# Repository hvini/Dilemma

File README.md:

---

The Dilemma is a vertical stagger low-profile keyboard with mods.

## Table of contents

- [Features](#features)
- [Versions](#versions)
- [Required components](#required-components)
  - [3d prints - cases](#3d-prints---cases)
  - [Electronics](#electronics)
  - [Procyon mod](#procyon-mod)
  - [Cirque Trackpad mod](#cirque-trackpad-mod)
  - [Cases](#cases)
    - [Acrylic midplate (v2 only)](#acrylic-midplate-v2-only)
  - [Metal plates](#metal-plates)
  - [Community mods](#community-mods)
  - [Build guide](#build-guide)
  - [Forks](#forks)

---

# Features

- heavy pinky stagger
- MX and choc compatible
- version with hotswap
- underglow RGB, per-key RGB
- 2 Rotary encoders on thumb clusters
- connectors for OLED, LCD

# Versions

There are multiple versions of the dilemma:

| Folder          | Name                   | Size  | PCBA | Trackpad | Switches         | Additional features                          |
| --------------- | ---------------------- | ----- | ---- | -------- | ---------------- | -------------------------------------------- |
| `3x5_2`         | Dilemma DIY V2         | 3x5+2 | no   | Cirque   | MX, Choc V1      |                                              |
| `3x5_2_trackball` | Dilemma DIY V2 trackball | 3x5+2 | no | Cirque, trackball | MX, Choc V1 | [Trackball header](3x5_2_trackball/README.md) |
| `3x5_3`         | Dilemma V2             | 3x5+3 | yes  | Cirque   | MX, Choc V1      | Underglow, per-key RGB, rotary encoders      |
| `3x5_3_procyon` | Dilemma V3 hotswap     | 3x5+3 | yes  | Procyon  | Choc V1, hotswap | Underglow, per-key RGB, rotary encoders, VIK |
| `4x6_4`         | Dilemma MAX            | 4x6+4 | yes  | Cirque   | MX, Choc V1      | Underglow, per-key RGB, rotary encoders      |
| `4x6_4_procyon` | Dilemma MAX V3 hotswap | 4x6+4 | yes  | Procyon  | Choc V1, hotswap | Underglow, per-key RGB, rotary encodersk VIK |

# Required components

## 3d prints - cases

You can find the required 3d prints in the `mechanical` folder.

Most cases require a transparent mid layer to look good. You can either print it, or order it cut in acrylic.

## Electronics

The new revisions are made to be PCBA'd, you can find the gerber, BOM and POS files in the [Releases](https://github.com/bastardkb/dilemma/releases) section.

## Procyon mod

The `dilemma v3 hotswap` is made to work with a [Procyon PCB](https://github.com/bstiq/procyon).

## Cirque Trackpad mod

This mod uses I2C on the DIY version, and SPI on the assembled version.

The DIY version requires removing some resistors from the trackpad:

- R1
- R7 and R8 if you are using a microcontroller that runs on 5V

When installing the trackpad mod, you will need:

| Part name           | Amount | Link / source           |
| ------------------- | ------ | ----------------------- |
| M3 screw, torx, 6mm | 4      | Conrad                  |
| M3x5x5 screw insert | 4      | Aliexpress              |
| 3d printed parts    |        | See `mechanical` folder |
| 40mm cirque trackpad, curved    |        | |

If building the PCBA version, you will also need:

| Part name                                                     | Amount | Link / source |
| ------------------------------------------------------------- | ------ | ------------- |
| 12-position FPC cable, 0.5mm pitch, same side contacts, 100mm, type-B | 1      | Farnell       |

If building the DIY version, you will also need:

| Part name               | Amount | Link / source |
| ----------------------- | ------ | ------------- |
| SOD123 Resistor, 5kOhms | 2      |               |
| Cables                  |        |               |

## Cases

### Acrylic midplate (v2 only)

This case is only compatible with the assembled_v2 version !

Add an underglow effect and a beautiful view into the PCB with those acrylic midplates.

## Metal plates

Optional metal plates enables the use of tripods through magsafe magnets.

Order the [metal plates](mechanical/plates/v2/bottom_metal.dxf) in 3mm thickness. The metal needs to be *magnetized* !
Grab the appropriate DXF from the matched folder.

You will need:

| Part name              | Amount | Details           |
| ---------------------- | ------ | ----------------- |
| Metal plates           | 2      | 3mm               |
| Tripods                | 2      | Neewer Z flex     |
| Magsafe tripod adapter | 2      | Amazon/Aliexpress |

## Community mods

There are a range of community mods available (hex plates, covers...).

You can find more information in the readme in the `mechanical/community mods` folder.

## Build guide

https://docs.bastardkb.com/bg_dilemma/intro.html

## Forks

- [3x6 version](https://github.com/bstiq/Dilemma_3x6/)
- [3x5 + 3 version](https://github.com/dixls/Dilemma-3mod)

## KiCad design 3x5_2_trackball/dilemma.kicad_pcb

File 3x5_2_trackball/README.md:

# Dilemma DIY V2 - trackball

The `3x5_2` DIY board with its unused trackball connector (J7) placed and routed. Everything else, including the outline, is unchanged.

**Order:** upload `dilemma_3x5_2_trackball_gerber.zip`. The board is reversible, so one design makes both halves. On the left half, leave J7 empty.

KiCad files need KiCad 8 or newer.

Build guide with BOM, for OLED left and trackball right (Brazilian Portuguese): [guia_de_montagem.md](guia_de_montagem.md)

## J7 pinout

J7 is a 2x3, 2.54mm header with through-hole pads, so you can solder from either face. Each pin is labelled on the silkscreen.

| Pin | Silk | Signal   | Controller pin (RP2040) |
| --- | ---- | -------- | ----------------------- |
| 1   | V+   | Vcc      | VCC (3.3V)              |
| 2   | CK   | SPI SCK  | GP22                    |
| 3   | MI   | SPI MISO | GP20                    |
| 4   | MO   | SPI MOSI | GP23                    |
| 5   | CS   | SPI CS   | GP21                    |
| 6   | G    | GND      | GND                     |

These are the same GPIOs as the PCBA trackball schematic (`3x5_3_trackball/schematic.pdf`). The pin order differs from the J7 in the `3x5_2` schematic, because a 2x3 header needs this order to route without crossings.

Check that your sensor board accepts 3.3V on V+.

## Mechanical notes

- `mechanical/trackball` parts screw into H6-H9, the four Cirque mod holes. The hole pattern is the same as on the PCBA board.
- On the right half, the B.Cu face points up, so the holder goes on that face.
- The ball sits over the controller, so the holder can't be bolted flat. Raise it on M3x10 female-female standoffs. The 10mm is an estimate, so dry-fit the controller and sensor before final assembly.
- J7 sits under the holder plate. Solder wires directly, or use a low-profile header.
- Use `mechanical/cases/3x5_2/thin` as the case. The `3x5_3_trackball` case matches the switches, H2 and the USB opening, but its contour wall has no opening for the TRRS jack, and its bottom plate sits against the solder joints.
- J7 is close to the J3 battery connector: their courtyards overlap by 0.5mm, but the parts themselves should clear by about 0.45mm.

## Firmware

Trackball only: enable the PMW33xx driver on SPI0 with the pins above, and set the right half as the pointing side.

Cirque on the left and trackball on the right: QMK allows one `POINTING_DEVICE_DRIVER` per build, so this needs `POINTING_DEVICE_DRIVER = custom` with your own code calling both sensors. No firmware is included here, and this combination has not been tested.

## Trackball parts

Sizes are measured from the STLs; the repo has no parts list.

| Part                                   | Qty | Notes                                 |
| -------------------------------------- | --- | ------------------------------------- |
| PMW3360 board with LM19-LSI lens       | 1   | Must fit under the holder's 19x24mm window |
| 34mm trackball                         | 1   | Holder cavity fits a 34mm ball        |
| MR63ZZ bearing (3x6x2.5mm)             | 3   | Size inferred from the 2.6mm wide slots |
| 3mm pin, 8mm long                      | 3   | Bearing axles                         |
| M3 screws, nuts and standoffs          | 4   | Length depends on the standoff height |

The holder has no screw posts for the sensor board. The board has to be fixed under the plate with the lens in the window, about 2.4mm from the ball (datasheet figure, from memory).

To reuse a Charybdis sensor PCB with the unmodified `mechanical/trackball` parts:

- The board is about 42mm across, so it overlaps H7 and H8. Use only three standoffs, at H6, H7 and H9, and leave H8 empty.
- Place the lens in the holder window with the board's 6-pin header on the J7 side.
- Mark H7 on the board's rim through the holder's hole, then file a notch about 3mm deep there. This spot has no copper within about 6mm of the hole centre, but dry-fit before cutting.
- Fix the board under the plate with double-sided tape about 0.5mm thick. This also sets the lens height to match the Charybdis.
- Wire 3.3V to V+, GND to G, SCK to CK, MISO to MI, MOSI to MO and SS to CS.

## Assembly warnings

- Jumpers JP1-JP8: solder one face only, on the left half only. Each header pin has two jumpers, one per face, so soldering both shorts signals to power or GND.
- OLED on the left half: with the F-face jumpers (JP1, JP3, JP5, JP7) and the F face up, the O2 pins read SDA, SCL, VCC, GND from left to right, with the controller above O2. Check this against the labels on your module, because VCC and GND positions vary between modules.
- Fit the right half's reset button on the bottom face (F side). The top is covered by the holder.
- Never plug or unplug the TRRS cable with USB connected. It carries 3.3V.
- Under the PCB, use low-head M3 screws at H6, H7 and H9. The `3x5_2/thin` case has about 3.4mm of room there.

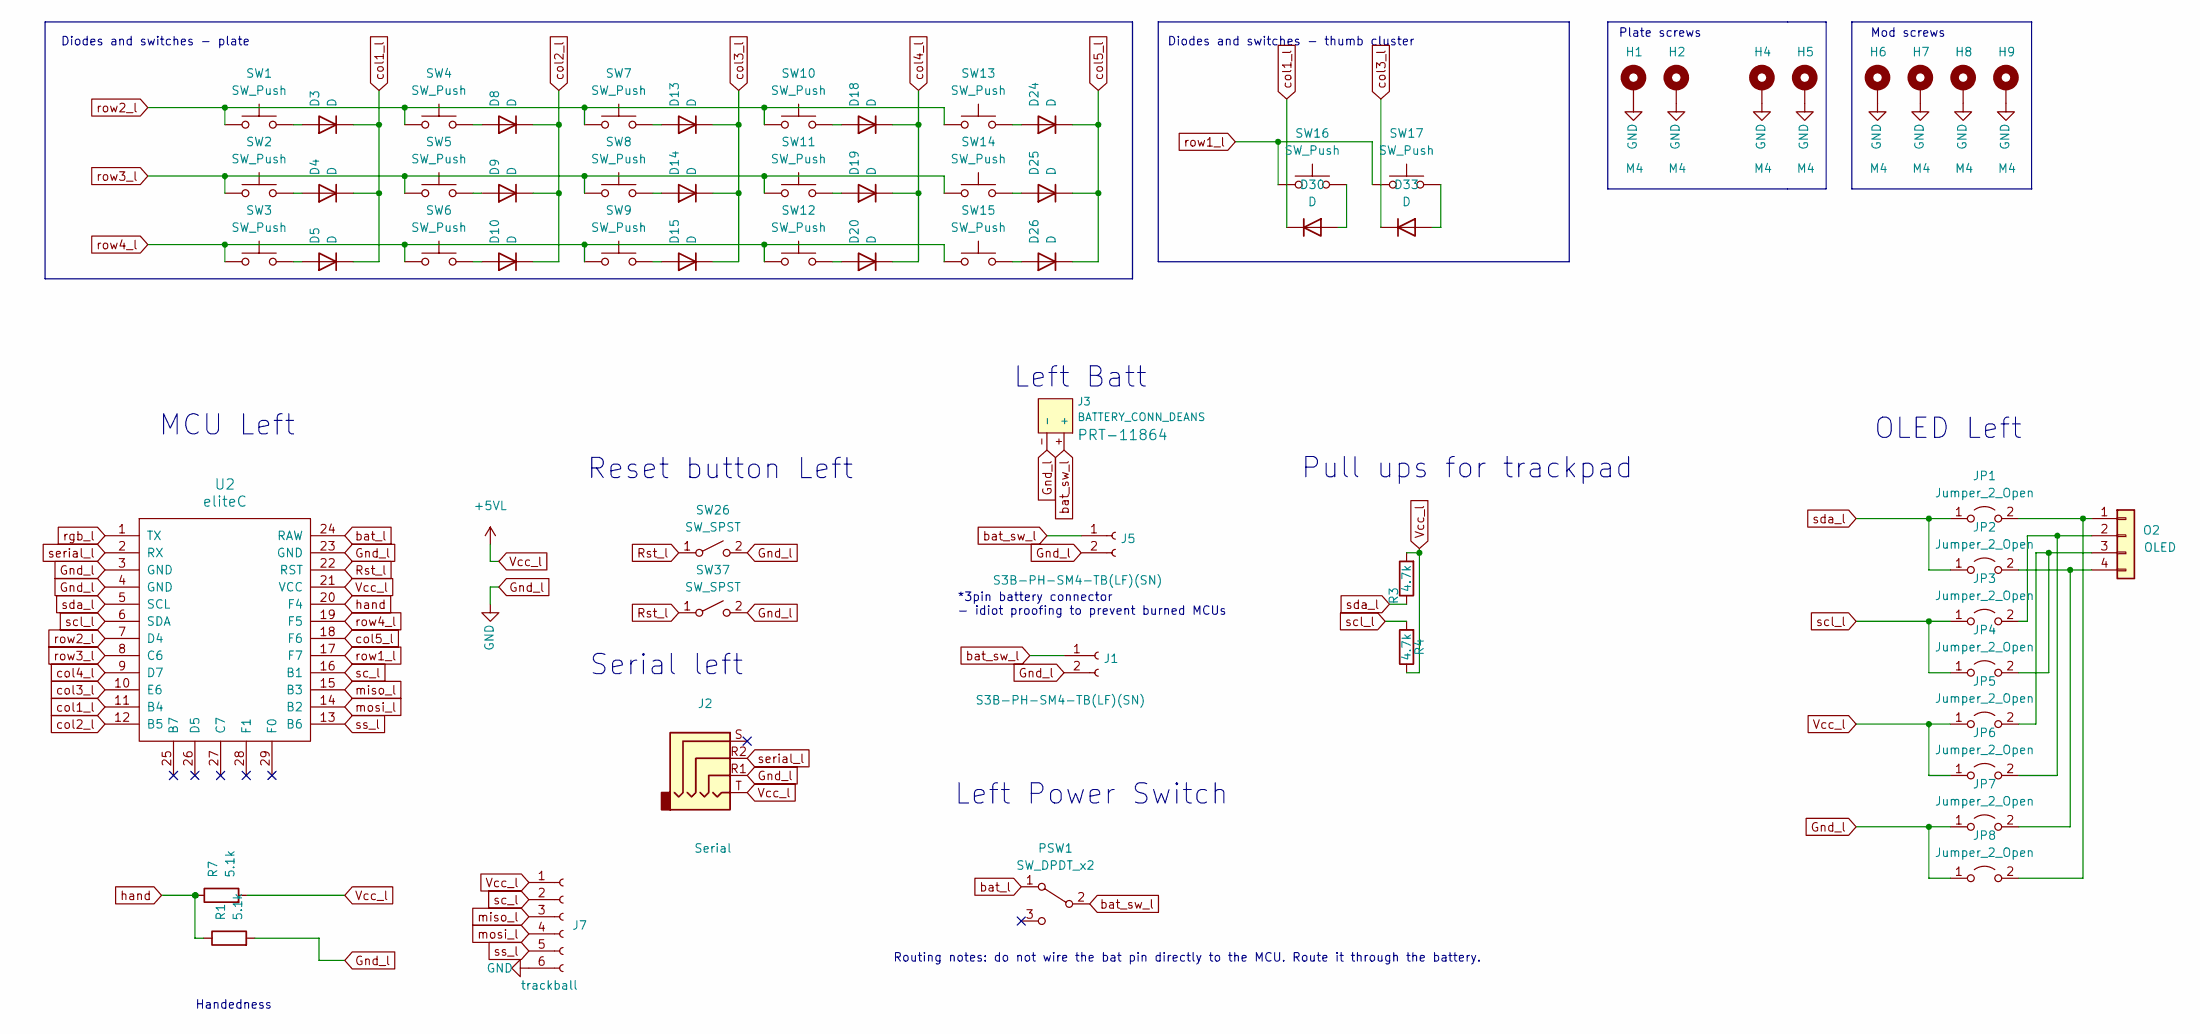
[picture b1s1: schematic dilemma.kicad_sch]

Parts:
D3, D4, D5, D8, D9, D10, D13, D14, D15, D18, D19, D20, D24, D25, D26, D30, D33: D; D_1206_handsolder_reversible
H1, H2, H4, H5, H6, H7, H8, H9: M4; MountingHole_3mm_Pad_thin
J1, J5: S3B-PH-SM4-TB(LF)(SN); JST_SH_BM02B-SRSS-TB_1x02-1MP_P1.00mm_Vertical; LCSC C265101
J2: Serial; Jack_3.5mm_PJ320E_Horizontal_reversible
J3: BATTERY_CONN_DEANS; battery_connector_THT
J7: trackball; PinHeader_2x03_P2.54mm_Vertical
JP1, JP2, JP3, JP4, JP5, JP6, JP7, JP8: Jumper_2_Open; SolderJumper-2_P1.3mm_Open_RoundedPad1.0x1.5mm
O2: OLED; PinHeader_1x04_P2.54mm_Vertical
PSW1: SW_DPDT_x2; Switch_MSK-12C01-07; LCSC C431540
R1, R7: 5.1k; R_1206_handsolder; JLCPCB BOM 1
R3, R4: 4.7k; R_1206_handsolder_reversible; LCSC C269746
SW1, SW2, SW3, SW4, SW5, SW6, SW7, SW8, SW9, SW10, SW11, SW12, SW13, SW14, SW15, SW16, SW17: SW_Push; SW_MX_choc
SW26, SW37: SW_SPST; SW_Push_1P1T_NO_6x6mm_H9.5mm
U2: eliteC; pro-micro

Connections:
Gnd_l: H1.1, H2.1, H4.1, H5.1, H6.1, H7.1, H8.1, H9.1, J1.2, J2.R1, J3.-, J5.2, J7.6, JP7.1 (A), JP8.1 (A), R1.2, SW26.2 (B), SW37.2 (B), U2.3 (GND), U2.4 (GND), U2.23 (GND)
unnamed: D3.2 (A), SW1.2
unnamed: D4.2 (A), SW2.2
unnamed: D5.2 (A), SW3.2
unnamed: D8.2 (A), SW4.2
unnamed: D9.2 (A), SW5.2
unnamed: D10.2 (A), SW6.2
unnamed: D13.2 (A), SW7.2
unnamed: D14.2 (A), SW8.2
unnamed: D15.2 (A), SW9.2
unnamed: D18.2 (A), SW10.2
unnamed: D19.2 (A), SW11.2
unnamed: D20.2 (A), SW12.2
unnamed: D24.2 (A), SW13.2
unnamed: D25.2 (A), SW14.2
unnamed: D26.2 (A), SW15.2
unnamed: D30.2 (A), SW16.2
unnamed: D33.2 (A), SW17.2
unnamed: JP1.2 (B), JP8.2 (B), O2.1
unnamed: JP2.2 (B), JP7.2 (B), O2.4
unnamed: JP3.2 (B), JP6.2 (B), O2.2
unnamed: JP4.2 (B), JP5.2 (B), O2.3
Rst_l: SW26.1 (A), SW37.1 (A), U2.22 (RST)
Vcc_l: J2.T, J7.1, JP5.1 (A), JP6.1 (A), R3.2, R4.1, R7.2, U2.21 (VCC)
bat_l: PSW1.1 (A), U2.24 (RAW)
bat_sw_l: J1.1, J3.+, J5.1, PSW1.2 (B)
col1_l: D3.1 (K), D4.1 (K), D5.1 (K), D30.1 (K), U2.11 (B4)
col2_l: D8.1 (K), D9.1 (K), D10.1 (K), U2.12 (B5)
col3_l: D13.1 (K), D14.1 (K), D15.1 (K), D33.1 (K), U2.10 (E6)
col4_l: D18.1 (K), D19.1 (K), D20.1 (K), U2.9 (D7)
col5_l: D24.1 (K), D25.1 (K), D26.1 (K), U2.18 (F6)
hand: R1.1, R7.1, U2.20 (F4)
miso_l: J7.3, U2.15 (B3)
mosi_l: J7.4, U2.14 (B2)
rgb_l: U2.1 (TX)
row1_l: SW16.1, SW17.1, U2.17 (F7)
row2_l: SW1.1, SW4.1, SW7.1, SW10.1, SW13.1, U2.7 (D4)
row3_l: SW2.1, SW5.1, SW8.1, SW11.1, SW14.1, U2.8 (C6)
row4_l: SW3.1, SW6.1, SW9.1, SW12.1, SW15.1, U2.19 (F5)
sc_l: J7.2, U2.16 (B1)
scl_l: JP3.1 (A), JP4.1 (A), R4.2, U2.6 (SDA)
sda_l: JP1.1 (A), JP2.1 (A), R3.1, U2.5 (SCL)
serial_l: J2.R2, U2.2 (RX)
ss_l: J7.5, U2.13 (B6)

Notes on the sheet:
MCU Left
Left Batt
Handedness
Plate screws
Routing notes: do not wire the bat pin directly to the MCU. Route it through the battery.
Serial left
Diodes and switches - plate
Reset button Left
Pull ups for trackpad
Mod screws
Left Power Switch
OLED Left
Diodes and switches - thumb cluster
*3pin battery connector - idiot proofing to prevent burned MCUs

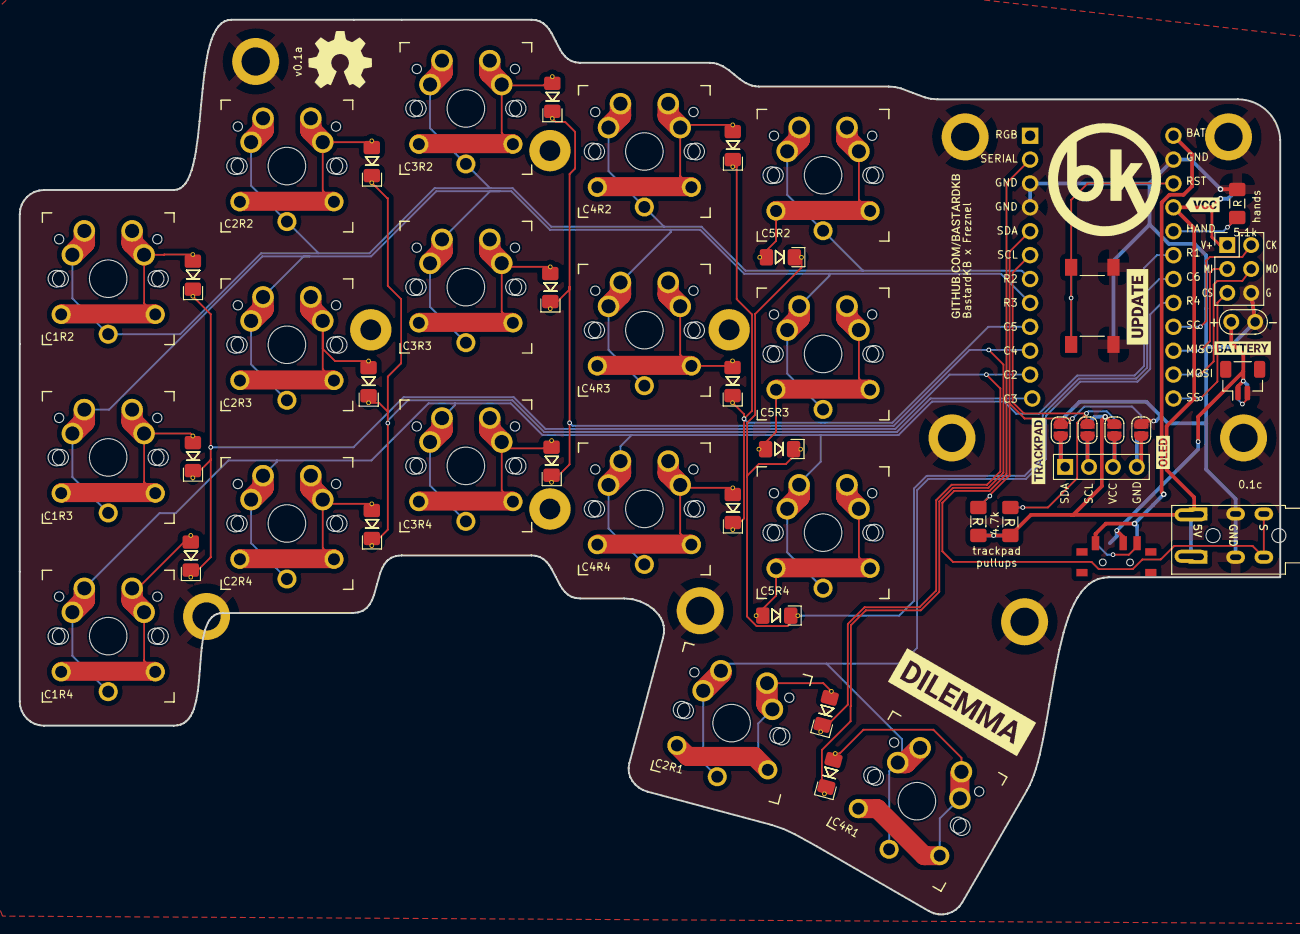
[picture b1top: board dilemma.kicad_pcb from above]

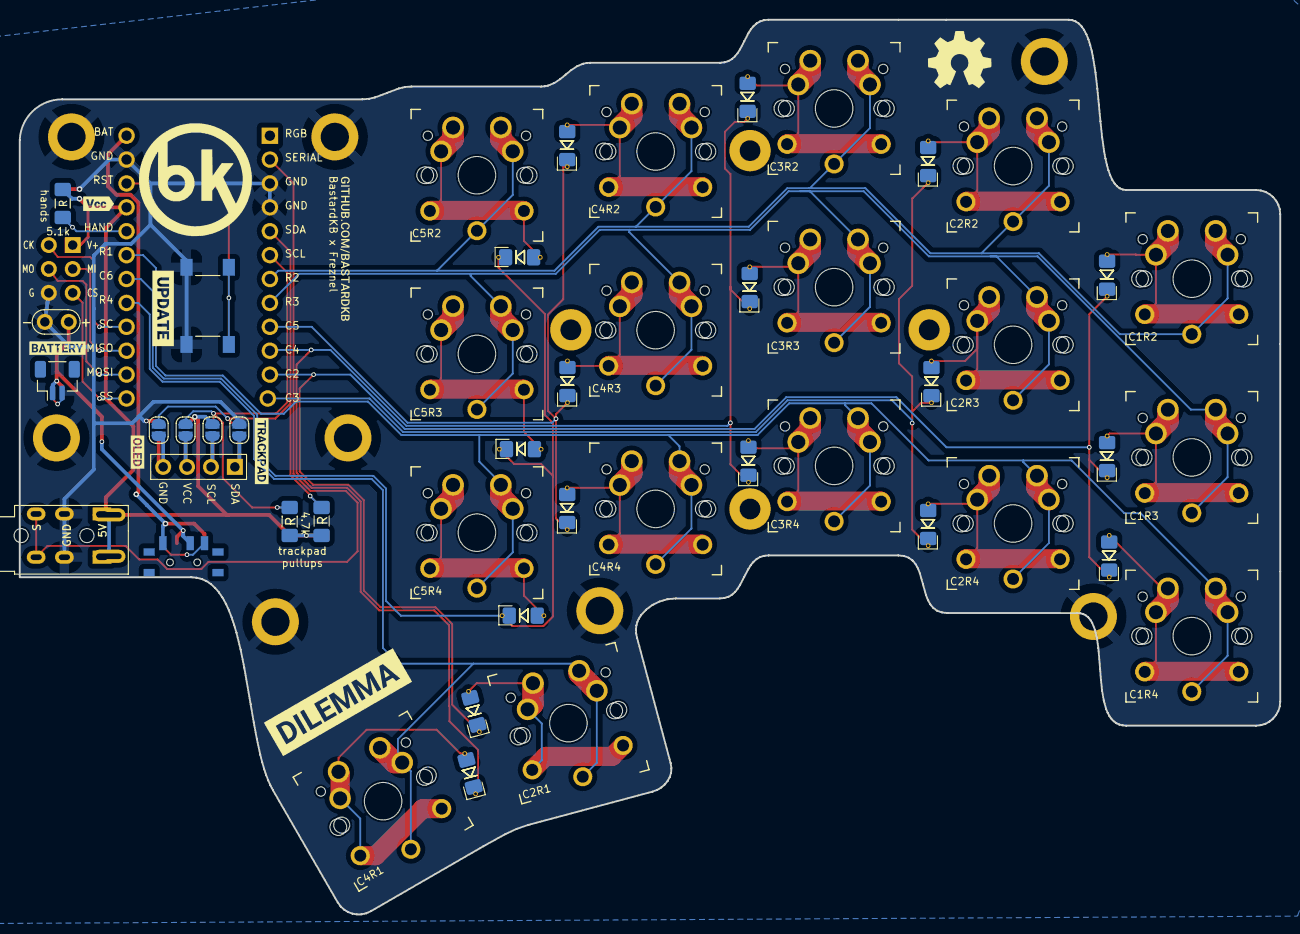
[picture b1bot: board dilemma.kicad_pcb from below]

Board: 2 copper layers, 134.0 x 95.1 mm, 78 parts (15 on the bottom side), 43 nets.

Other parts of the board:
kibuzzard-61F01A92, kibuzzard-61F01A92#2: G***; kibuzzard-61F01A92
kibuzzard-61F01C84, kibuzzard-61F01C84#2: G***; kibuzzard-61F01C84
kibuzzard-628D3AA1: G***; kibuzzard-628D3AA1
kibuzzard-628D396A: G***; kibuzzard-628D396A
kibuzzard-628DFB5F, kibuzzard-628DFB5F#2: G***; kibuzzard-628DFB5F
kibuzzard-628DFB48, kibuzzard-628DFB48#2: G***; kibuzzard-628DFB48
kibuzzard-628DFB95, kibuzzard-628DFB95#2: G***; kibuzzard-628DFB95
kibuzzard-628E0199, kibuzzard-628E0199#2: G***; kibuzzard-628E0199
